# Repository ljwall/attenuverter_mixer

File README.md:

# Eurorack attenuverter and mixer module

Four channels, each with input -> attenuverter control -> output. Each input is
normaled to +5v if there is no jack in the input. Each output channel (after the
attenuverting stage) is also sent to a summing mixer, and to an analogue logic
or, a.k.a. the peaks part from [peaks and troughs](https://www.elby-designs.com/webtek/cgs/cgs26/cgs26_analogic.html).

If an individual output chnanel is patched, it's removed from the summing mixer
and the peaks output.

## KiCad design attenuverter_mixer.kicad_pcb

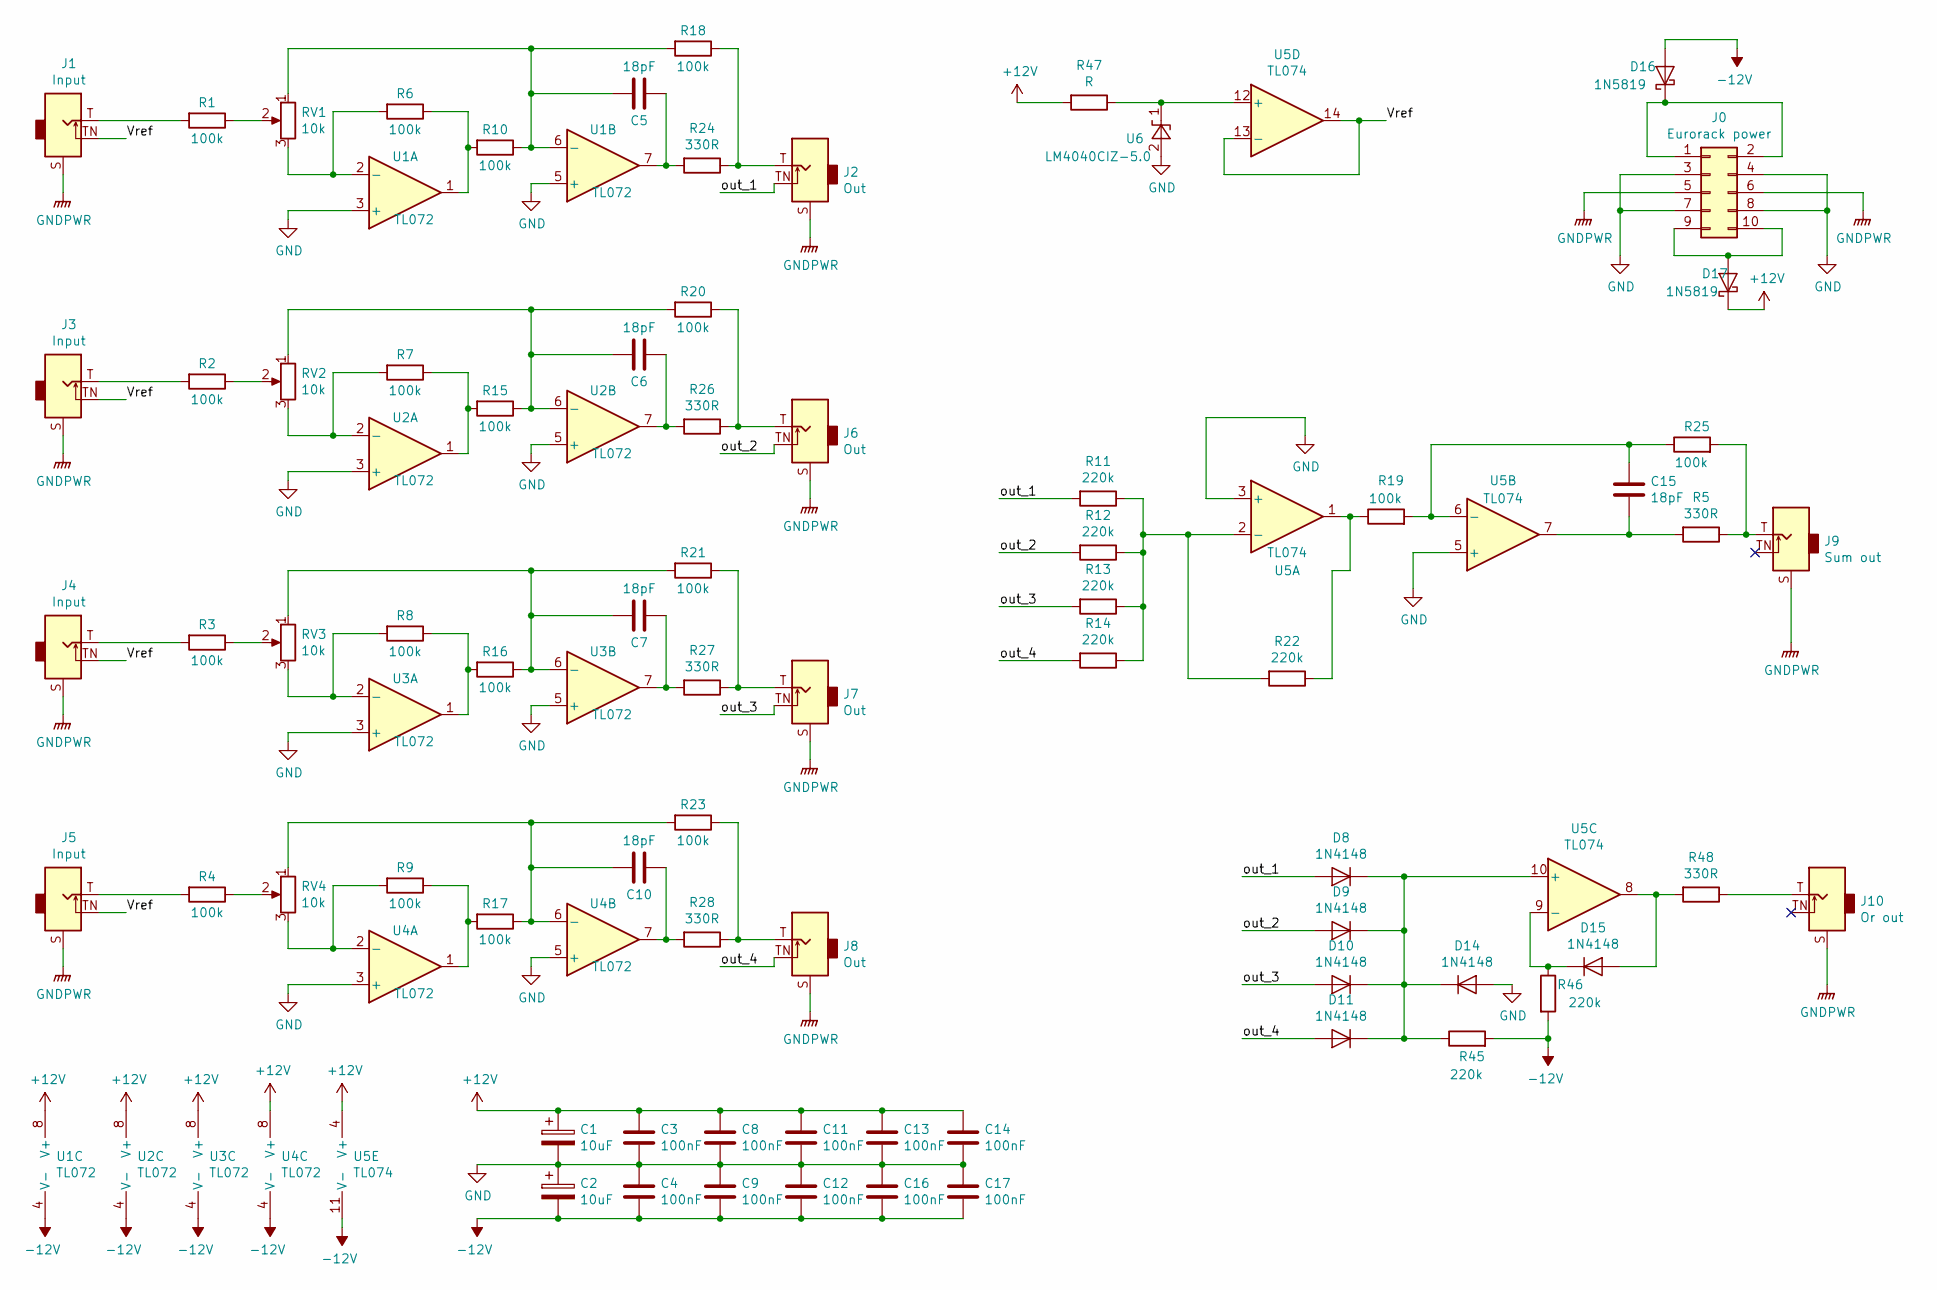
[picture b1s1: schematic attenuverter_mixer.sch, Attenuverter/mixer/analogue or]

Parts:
C1, C2: 10uF; CP_Radial_D5.0mm_P2.00mm
C3, C4, C8, C9, C11, C12, C13, C14, C16, C17: 100nF; C_Disc_D3.0mm_W1.6mm_P2.50mm
C5, C6, C7, C10, C15: 18pF; C_Disc_D3.0mm_W2.0mm_P2.50mm
D8, D9, D10, D11, D14, D15: 1N4148; D_DO-35_SOD27_P7.62mm_Horizontal
D16, D17: 1N5819; D_DO-41_SOD81_P10.16mm_Horizontal
J0: Eurorack power; PinSocket_2x05_P2.54mm_Vertical
J1, J3, J4, J5: Input; Jack_3.5mm_QingPu_WQP-PJ398SM_Vertical_CircularHoles
J2, J6, J7, J8: Out; Jack_3.5mm_QingPu_WQP-PJ398SM_Vertical_CircularHoles
J9: Sum out; Jack_3.5mm_QingPu_WQP-PJ398SM_Vertical_CircularHoles
J10: Or out; Jack_3.5mm_QingPu_WQP-PJ398SM_Vertical_CircularHoles
R1, R2, R3, R4, R6, R7, R8, R9, R10, R15, R16, R17, R18, R19, R20, R21, R23, R25: 100k; R_1206_3216Metric_Pad1.42x1.75mm_HandSolder
R5, R48: 330R; R_Axial_DIN0309_L9.0mm_D3.2mm_P2.54mm_Vertical
R11, R12, R13, R14, R22, R45, R46: 220k; R_1206_3216Metric_Pad1.42x1.75mm_HandSolder
R24, R26, R27, R28: 330R; R_Axial_DIN0309_L9.0mm_D3.2mm_P12.70mm_Horizontal
R47: R; R_Axial_DIN0309_L9.0mm_D3.2mm_P2.54mm_Vertical
RV1, RV2, RV3, RV4: 10k; Potentiometer_Alpha_RD901F-40-00D_Single_Vertical
U1, U2, U3, U4: TL072; SOIC-8_3.9x4.9mm_P1.27mm
U5: TL074; SOIC-14_3.9x8.7mm_P1.27mm
U6: LM4040CIZ-5.0; TO-92_Inline

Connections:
+12V: C1.1, C3.1, C8.1, C11.1, C13.1, C14.1, D17.1 (K), R47.2, U1.8 (V+), U2.8 (V+), U3.8 (V+), U4.8 (V+), U5.4 (V+)
-12V: C2.2, C4.2, C9.2, C12.2, C16.2, C17.2, D16.2 (A), R45.2, R46.2, U1.4 (V-), U2.4 (V-), U3.4 (V-), U4.4 (V-), U5.11 (V-)
/Vref: J1.TN, J3.TN, J4.TN, J5.TN, U5.13 (-), U5.14
/out_1: D8.2 (A), J2.TN, R11.2
/out_2: D9.2 (A), J6.TN, R12.2
/out_3: D10.2 (A), J7.TN, R13.2
/out_4: D11.2 (A), J8.TN, R14.2
GND: C1.2, C2.1, C3.2, C4.1, C8.2, C9.1, C11.2, C12.1, C13.2, C14.2, C16.1, C17.1, D14.2 (A), J0.3, J0.4, J0.7, J0.8, U1.3 (+), U1.5 (+), U2.3 (+), U2.5 (+), U3.3 (+), U3.5 (+), U4.3 (+), U4.5 (+), U5.3 (+), U5.5 (+), U6.2 (A)
GNDPWR: J0.5, J0.6, J1.S, J2.S, J3.S, J4.S, J5.S, J6.S, J7.S, J8.S, J9.S, J10.S
unnamed: C5.1, R24.2, U1.7
unnamed: C5.2, R10.1, R18.2, RV1.1, U1.6 (-)
unnamed: C6.1, R26.2, U2.7
unnamed: C6.2, R15.1, R20.2, RV2.1, U2.6 (-)
unnamed: C7.1, R27.2, U3.7
unnamed: C7.2, R16.1, R21.2, RV3.1, U3.6 (-)
unnamed: C10.1, R28.2, U4.7
unnamed: C10.2, R17.1, R23.2, RV4.1, U4.6 (-)
unnamed: C15.1, R5.2, U5.7
unnamed: C15.2, R19.2, R25.1, U5.6 (-)
unnamed: D8.1 (K), D9.1 (K), D10.1 (K), D11.1 (K), D14.1 (K), R45.1, U5.10 (+)
unnamed: D15.1 (K), R46.1, U5.9 (-)
unnamed: D15.2 (A), R48.2, U5.8
unnamed: D16.1 (K), J0.1, J0.2
unnamed: D17.2 (A), J0.9, J0.10
unnamed: J1.T, R1.2
unnamed: J2.T, R18.1, R24.1
unnamed: J3.T, R2.2
unnamed: J4.T, R3.2
unnamed: J5.T, R4.2
unnamed: J6.T, R20.1, R26.1
unnamed: J7.T, R21.1, R27.1
unnamed: J8.T, R23.1, R28.1
unnamed: J9.T, R5.1, R25.2
unnamed: J10.T, R48.1
unnamed: R1.1, RV1.2
unnamed: R2.1, RV2.2
unnamed: R3.1, RV3.2
unnamed: R4.1, RV4.2
unnamed: R6.2, RV1.3, U1.2 (-)
unnamed: R7.2, RV2.3, U2.2 (-)
unnamed: R8.2, RV3.3, U3.2 (-)
unnamed: R9.2, RV4.3, U4.2 (-)
unnamed: R6.1, R10.2, U1.1
unnamed: R11.1, R12.1, R13.1, R14.1, R22.2, U5.2 (-)
unnamed: R7.1, R15.2, U2.1
unnamed: R8.1, R16.2, U3.1
unnamed: R9.1, R17.2, U4.1
unnamed: R19.1, R22.1, U5.1
unnamed: R47.1, U5.12 (+), U6.1 (K)

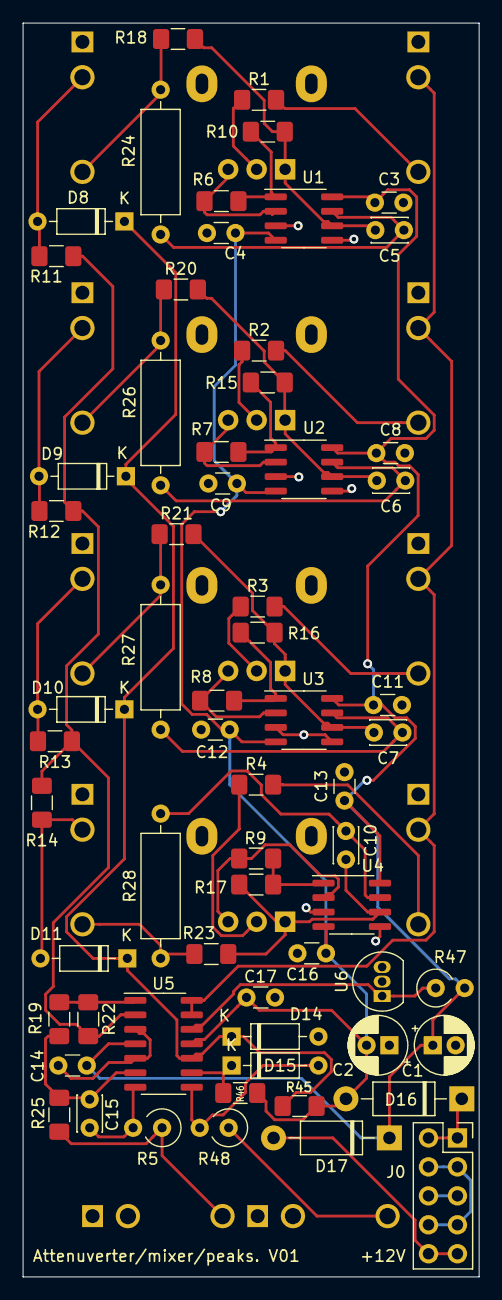
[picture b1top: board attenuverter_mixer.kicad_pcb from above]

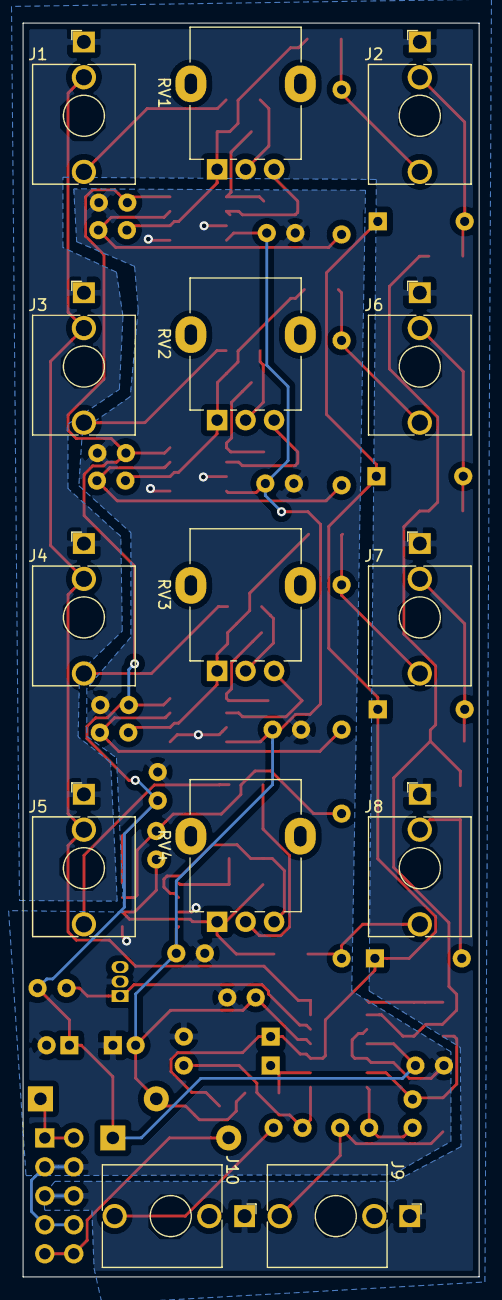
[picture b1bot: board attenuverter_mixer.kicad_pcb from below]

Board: 2 copper layers, 40.0 x 110.0 mm, 78 parts (14 on the bottom side), 49 nets.

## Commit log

2019-09-15 Add readme
2019-09-15 Add the missing 5v voltage reference
2019-09-15 Adjust peaks pull down resistors up to 1M
2019-09-24 assorted updates
2019-09-24 Remove TVS diodes from i/o
2019-09-24 remove two more TVS diodes; remove input resistors; use SM resistors
2019-09-27 Where it's at, just before changing the op amp configuration
2019-10-04 V01 as fabricated
    - Use surface mount 100K and 220K to allow single board.
    - Drop offset pots --- just have atteunuvert controls on each channel.

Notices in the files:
attenuverter_mixer.sch:
https://creativecommons.org/licenses/by-sa/3.0/legalcode
License: CC BY-SA 3.0
